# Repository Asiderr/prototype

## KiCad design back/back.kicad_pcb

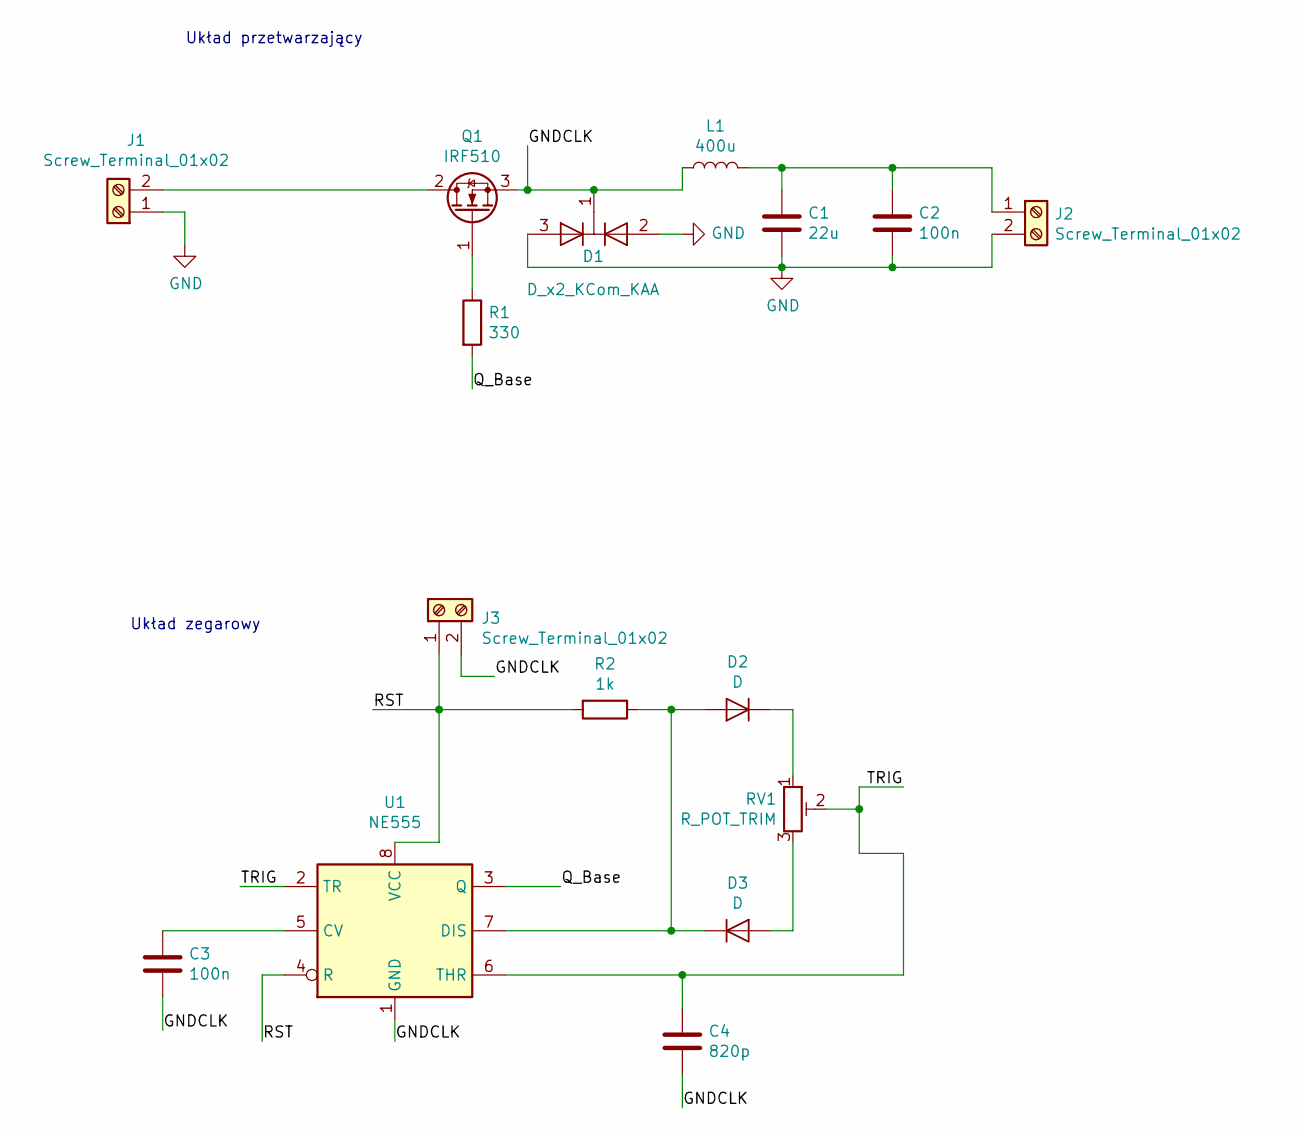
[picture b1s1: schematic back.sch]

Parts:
C1: 22u; CP_Axial_L11.0mm_D5.0mm_P18.00mm_Horizontal
C2, C3: 100n; C_Disc_D7.5mm_W5.0mm_P10.00mm
C4: 820p; C_0603_1608Metric_Pad1.05x0.95mm_HandSolder
D1: D_x2_KCom_KAA; TO-220-3_Vertical
D2, D3: D; D_DO-34_SOD68_P10.16mm_Horizontal
J1, J2, J3: Screw_Terminal_01x02; TerminalBlock_bornier-2_P5.08mm
L1: 400u; ind_W60mm_D19mm_P38mm
Q1: IRF510; TO-220-3_Vertical
R1: 330; R_Axial_DIN0207_L6.3mm_D2.5mm_P10.16mm_Horizontal
R2: 1k; R_Axial_DIN0207_L6.3mm_D2.5mm_P10.16mm_Horizontal
RV1: R_POT_TRIM; Potentiometer_Piher_PT-10-V10_Vertical
U1: NE555; DIP-8_W10.16mm_LongPads

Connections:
/GNDCLK: C3.2, C4.2, D1.1 (K), J3.2, L1.1, Q1.3 (S), U1.1 (GND)
/Q_Base: R1.2, U1.3 (Q)
/RST: J3.1, R2.2, U1.4 (R), U1.8 (VCC)
/TRIG: C4.1, RV1.2, U1.2 (TR), U1.6 (THR)
GND: C1.2, C2.2, D1.2 (A), D1.3 (A), J1.1, J2.2
unnamed: C1.1, C2.1, J2.1, L1.2
unnamed: C3.1, U1.5 (CV)
unnamed: D2.1 (K), RV1.1
unnamed: D2.2 (A), D3.1 (K), R2.1, U1.7 (DIS)
unnamed: D3.2 (A), RV1.3
unnamed: J1.2, Q1.2 (D)
unnamed: Q1.1 (G), R1.1

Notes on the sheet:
Układ przetwarzający
Układ zegarowy

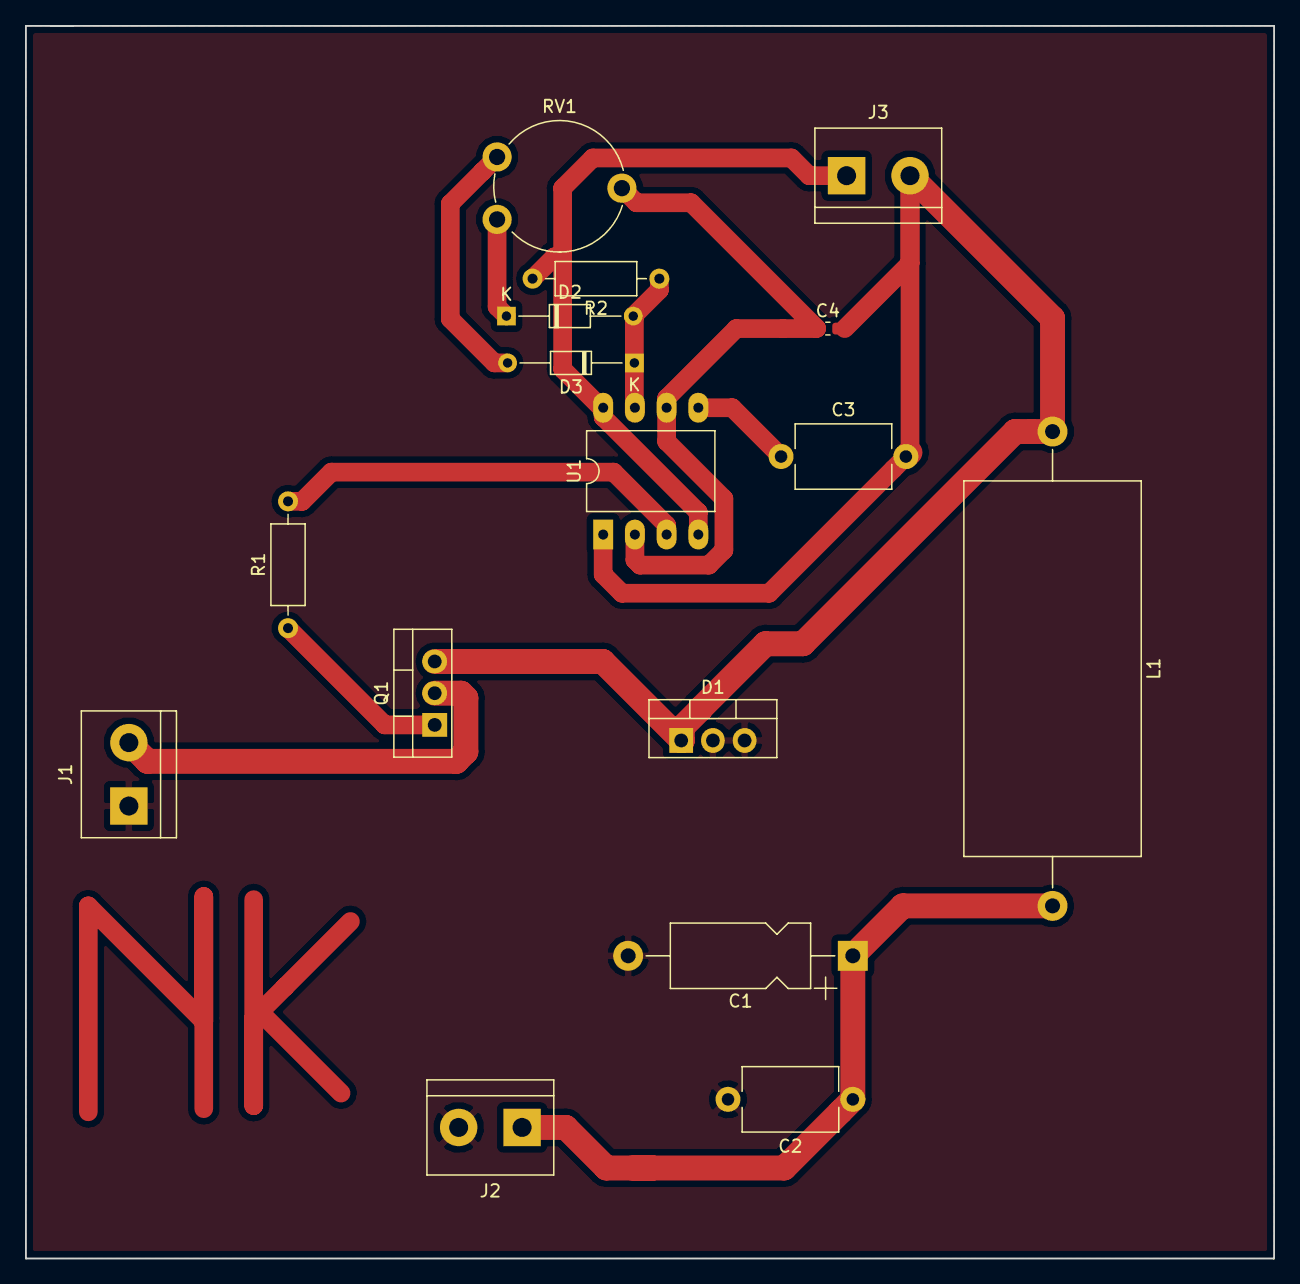
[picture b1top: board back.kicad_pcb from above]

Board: 2 copper layers, 100.0 x 98.8 mm, 16 parts (0 on the bottom side), 12 nets.

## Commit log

2019-04-12 init commit
2019-04-12 schematic ideal
2019-04-26 final v1
2019-05-15 Schema final
2019-05-15 Final version v2
2019-05-16 fight with gcodes
2019-05-17 zajecia
2019-06-10 wersja nie dzialajaca
2019-06-10 final 6.10
